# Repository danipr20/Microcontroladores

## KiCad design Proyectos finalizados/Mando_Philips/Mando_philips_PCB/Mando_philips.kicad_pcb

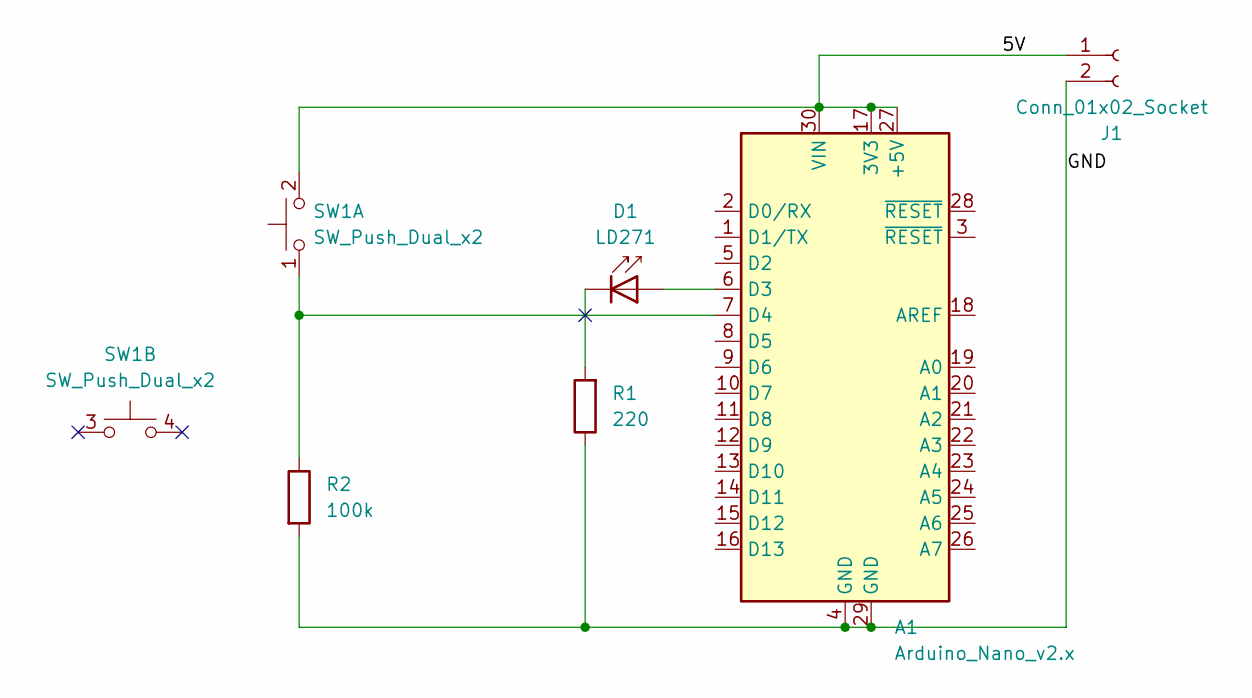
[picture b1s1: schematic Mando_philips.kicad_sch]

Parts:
A1: Arduino_Nano_v2.x; Arduino_Nano
D1: LD271; LED_D5.0mm_Horizontal_O1.27mm_Z3.0mm_IRGrey
J1: Conn_01x02_Socket; Molex_KK-254_AE-6410-02A_1x02_P2.54mm_Vertical
R1: 220; R_Axial_DIN0309_L9.0mm_D3.2mm_P12.70mm_Horizontal
R2: 100k; R_Axial_DIN0309_L9.0mm_D3.2mm_P12.70mm_Horizontal
SW1: SW_Push_Dual_x2; SW_PUSH_6mm_H8mm

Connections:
/5V: A1.17 (3V3), A1.27 (+5V), A1.30 (VIN), J1.1, SW1.2 (D)
/GND: A1.4 (GND), A1.29 (GND), J1.2, R1.1, R2.2
unnamed: A1.6 (D3), D1.2 (A)
unnamed: A1.7 (D4), R2.1, SW1.1 (C)
unnamed: D1.1 (K), R1.2

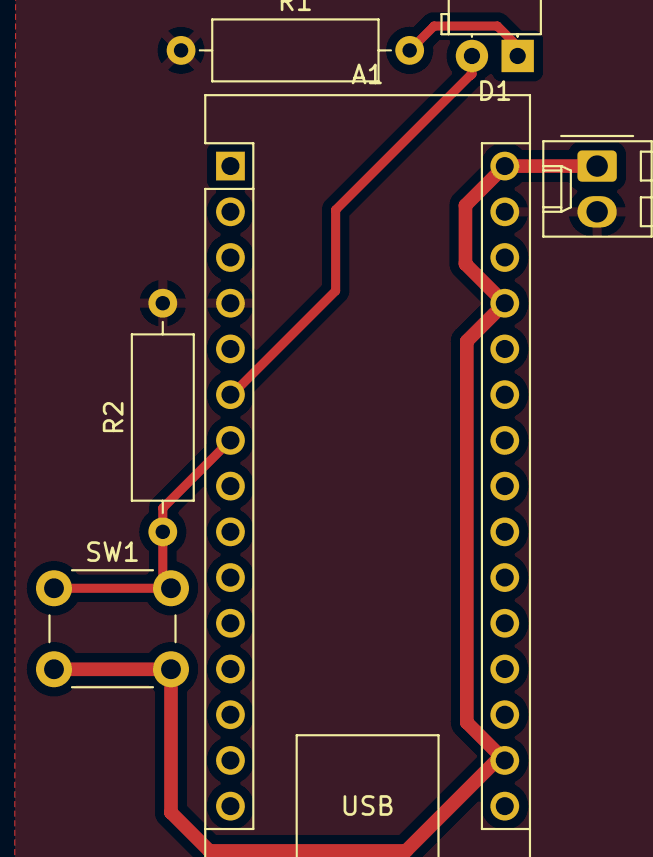
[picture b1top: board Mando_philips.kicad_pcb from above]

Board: 2 copper layers, 6 parts (0 on the bottom side), 5 nets.

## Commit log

2023-11-03 subida a git de proyectos de Arduino y ESP
2023-11-03 nuevos ficheros de IR (subida de archivos PC sobremesa)
2023-11-03 ir_emiter
2023-11-11 ir UNO y esp8266
2023-11-20 subida de varios programas
2023-11-24 creacion de programas nuevos
2023-11-25 sensores nuevos
2023-11-26 nuevos sensores y programa control de riego
2023-12-01 avance en proyecto "TERMOGRAFO", sensor dht11 funcional, falta implementar el analogico
2023-12-02 Implementación de lectura de archivo de configuración, modelo principal Termografo_NANO_TMP1820
2023-12-02 pequeña modificacion en Termografo_NANO_TMP1820
2024-01-11 actualizacion
2024-01-21 Subida de varios archivos
